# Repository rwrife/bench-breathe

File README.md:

# Bench Breathe

USB-powered ESP32-C3 workshop air-quality logger that tracks PM2.5 and VOC trends locally to help makers improve ventilation habits without cloud accounts.

## Overview

Bench Breathe is a low-voltage, local-first open-hardware project for hobby workshops and desk labs. It samples particulate and VOC indicators with temperature/humidity context, stores bounded trend history locally, and provides a local companion dashboard for setup, quality states, event notes, and explicit export.

**Bench Breathe is a non-certified advisory trend logger.** It does not determine whether air is safe and is not a medical, emergency, life-safety, or occupational-exposure instrument.

## Intended users and use cases

- Electronics hobbyists comparing trends during soldering or rework.
- 3D-printing users comparing baseline and active-print periods.
- Home workshop users recording manual actions such as opening a window or enabling an independently controlled extractor.
- Makers exporting their own local CSV/JSON data for troubleshooting and analysis.

## MVP workflow

1. Power the device from a reputable 5 V USB SELV source.
2. Connect from a phone/desktop browser on the local network or use USB serial fallback.
3. Complete time-bounded setup and baseline/warm-up prompts.
4. Record a work session and optional ventilation event labels.
5. Review local trends, freshness, quality states, and data gaps.
6. Export or delete local data through an explicit user action.

## Frozen MVP baseline

The normative baseline is in [`hardware/requirements.md`](hardware/requirements.md), with subsystem ownership, dependencies, evidence gates, and the risk register in [`PLAN.md`](PLAN.md).

Key constraints:

- USB 5 V SELV only; <=250 mA steady-state target and <=500 mA peak.
- PM2.5, VOC proxy/index, temperature, and humidity trend channels.
- Default 2 s acquisition, bounded local retention, and deterministic rollover.
- Local HTTP/JSON app interface with USB serial setup/recovery/export fallback.
- Offline sampling without mandatory internet, cloud account, or outbound telemetry.
- Editable KiCad hardware sources and schematic-owned Manufacturer/MPN BOM data.
- Advisory trend language only; static, simulation, bench, and field evidence remain distinct.

## Explicit non-goals and safety limits

- **No mains wiring or control.** No relays, fan switching, actuators, machinery control, or safety interlocks.
- **No hazardous-voltage or USB-PD operation.** The project is nominal 5 V USB SELV only.
- **No medical, emergency, fire/smoke/gas-alarm, life-safety, or occupational-limit function.**
- **No certified accuracy or safe/unsafe determination.** Placement, warm-up, drift, contamination, airflow, and faults can produce misleading data.
- **No mandatory cloud service or internet access.**
- Indoor, dry, non-condensing hobby-workshop use only; not for outdoor, explosive, or industrial-process environments.

Users must follow tool/material manufacturer guidance and appropriate ventilation and PPE practice independently of this device.

## Architecture at a glance

- **Hardware:** USB input/protection/regulation, ESP32-C3, PM/VOC/temp-humidity interfaces, status/input, debug/test access, PCB, and enclosure interface.
- **Firmware:** deterministic acquisition, validity states, bounded retention, atomic configuration, versioned local API, and serial recovery.
- **Companion web app:** setup, status/history, event notes, configuration, explicit export/delete, and accessible advisory messaging.
- **Shared protocol:** [`docs/protocol.md`](docs/protocol.md) is finalized contract v1 (HTTP + USB-serial shapes, units, limits, errors, authorization). The firmware baseline still streams the v0-compatible serial line; adoption is tracked in `docs/release-checklist.md` (T-1).

The device remains authoritative for sensor state, timestamps, configuration limits, and retained records. The app presents that contract and must not turn null/invalid values into apparently valid measurements. For the MVP, compiled app assets are served by the device for offline same-origin use. A physical, time-bounded setup action issues the per-device local credential; this reduces casual LAN access but does not make cleartext HTTP confidential or safe for internet exposure.

## Source tree

- `hardware/requirements.md` — normative MVP requirements and safety boundaries
- `hardware/kicad/bench-breathe.kicad_pro` — editable KiCad project container
- `hardware/kicad/bench-breathe.kicad_sch` — editable A0 electrical schematic and schematic-owned BOM-property source
- `hardware/kicad/bench-breathe.kicad_pcb` — planned editable PCB
- `hardware/component-selection.md` — exact M2 parts, manufacturer-datasheet checks, static power budget, and dated availability snapshot
- `firmware/` — device firmware and verification
- `app/` — local companion web app
- `docs/protocol.md` — device/app contract (v1)
- `docs/bring-up.md` — integration bring-up procedure, wiring/pinouts, calibration, troubleshooting matrix, and evidence ledger
- `docs/release-checklist.md` — fabrication/release artifact gates and open tracked items
- `bom/bom.csv` — generated stuffed-BOM export from schematic properties (regenerate with `python3 bom/export_bom.py`, gate with `python3 bom/verify_bom.py`)
- `bom/README.md` — BOM workflow, sourcing/pricing policy, and file roles
- `bom/non-schematic-items.csv` — enclosure, cables, fasteners, adapter, power supply, and PCB fab with explicit planning status

The current `bom/preliminary-bom.csv` is the issue-#2 planning list reconciled against the schematic (`Schematic_Refs`/`Reconciliation` columns). It is not a fabrication-ready BOM; `bom/bom.csv` is the export artifact.

## Project status

| Milestone | Status |
|---|---|
| M1 — Requirements, architecture, safety, and risk baseline | Baseline documented |
| M2 — Datasheet-backed component selection | Static selection complete; physical validation not started |
| M3 — Editable KiCad schematic and ERC | Complete: clean KiCad 9 ERC plus static validation and PDF review export |
| M4 — Schematic-source BOM export | Complete: `bom/bom.csv` generated from schematic properties with reproducibility + no-fabricated-price gate (`bom/verify_bom.py`) |
| M5 — PCB layout and DRC | A0 evidence board complete: 0 DRC violations with 15 documented unrouted stubs — **not fab release** (see `hardware/pcb-notes.md` §Residuals and `docs/release-checklist.md`) |
| M6 — Firmware baseline | Baseline implemented + natively verified (19 unit tests, pinned device build). Bench flash/flash-recovery and power gating on hardware not performed |
| M7 — Companion app baseline | App MVP + contract v1 complete; 13/13 contract tests against the dev simulator only — never run against a real device |
| M8 — Integration and bench bring-up | Bring-up procedure, wiring/pinouts, and troubleshooting published (`docs/bring-up.md`); all bench steps unexecuted — no prototype exists |
| M9 — Mature fabrication/release bundle | Gate checklist published (`docs/release-checklist.md`); fab artifacts blocked on A1 stub closure |

The editable A0 schematic and its static ERC/analyzer evidence are complete,
as is the A0 evidence PCB (0 DRC violations, 15 documented unrouted stubs —
not fab release), the natively verified firmware baseline, and the
contract-tested companion app (simulator-evidence only). PCB fab export,
simulation, firmware/app builds on hardware, assembly, bench measurement,
field results, and certification are not claimed. See
`docs/bring-up.md` (bench procedure and evidence ledger) and
`docs/release-checklist.md` (release gates and open tracked items).

## Development start

```bash
git clone https://github.com/rwrife/bench-breathe.git
cd bench-breathe
```

Review `hardware/requirements.md`, `PLAN.md`, and the issue backlog before implementing a subsystem. Work should proceed in dependency order and attach the evidence named by the relevant milestone; documentation alone does not satisfy a hardware or physical-test gate.

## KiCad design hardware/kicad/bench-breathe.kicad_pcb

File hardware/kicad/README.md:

# KiCad hardware sources

`bench-breathe.kicad_sch` is the editable A0 electrical schematic. It stores exact Manufacturer/MPN/LCSC/Datasheet/Package/BOM Comments fields and implements USB power/data/CC sensing, the fixed 3.3 V regulator, controller, sensors, programming/debug, local status/button, and named test points.

Project-local functional symbols and the SGP40 land pattern live under `lib/`; `generate_schematic.py` regenerates the editable source, and `validate_schematic.py` checks critical datasheet pin maps, net assignments, BOM properties, ERC JSON, and the PDF export.

Reproduce the static evidence from the repository root:

```bash
python3 -m venv /tmp/bench-breathe-ksa-env
/tmp/bench-breathe-ksa-env/bin/pip install -r hardware/kicad/requirements.txt
KICAD_SYMBOL_DIR=/usr/share/kicad/symbols /tmp/bench-breathe-ksa-env/bin/python hardware/kicad/generate_schematic.py
kicad-cli sch erc hardware/kicad/bench-breathe.kicad_sch --format json --output hardware/kicad/reports/erc.json --exit-code-violations
kicad-cli sch export pdf hardware/kicad/bench-breathe.kicad_sch --output hardware/kicad/exports/bench-breathe-schematic.pdf
KICAD_SYMBOL_DIR=/usr/share/kicad/symbols /tmp/bench-breathe-ksa-env/bin/python hardware/kicad/validate_schematic.py --erc hardware/kicad/reports/erc.json --footprint-dir /usr/share/kicad/footprints
```

The zero-violation ERC and validator are **static schematic evidence only**. They do not prove PCB routing, signal integrity, radio performance, power transients, assembly, sensor accuracy, or physical operation.

Re-run the metadata gate from the repository root with:

```bash
python3 hardware/scripts/verify_component_selection.py
```

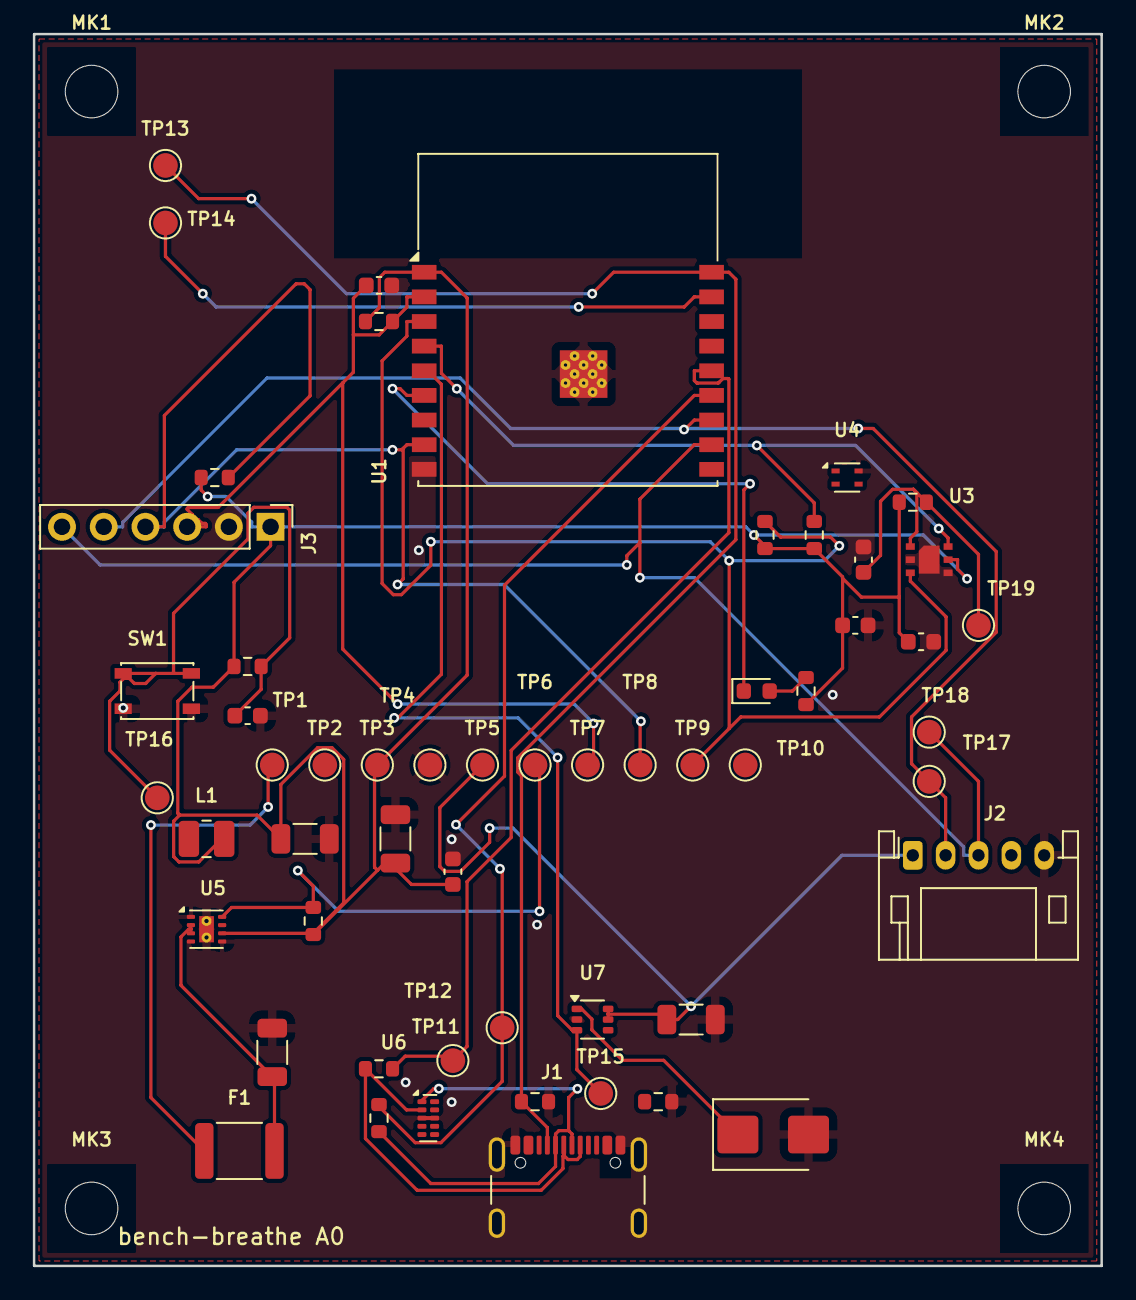
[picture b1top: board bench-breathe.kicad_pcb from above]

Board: 2 copper layers, 65.0 x 75.0 mm, 59 parts (0 on the bottom side), 24 nets.

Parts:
C1, C2, C3, C10: C_1206_3216Metric
C4, C5, C6, C7, C8, C9: C_0603_1608Metric
D1: D_SMB
D2: LED_0603_1608Metric
F1: Fuse_1812_4532Metric
J1: USB_C_Receptacle_GCT_USB4105-xx-A_16P_TopMnt_Hori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; USB_C_Receptacle_GCT_USB4105-xx-A_16P_TopMnt_Horizontal
J2: JST_PH_S5B-PH-K_1x05_P2.00mm_Horizontal
J3: PinHeader_1x06_P2.54mm_Vertical
L1: L_1008_2520Metric
MK1, MK2, MK3, MK4: MountingHole_3.2mm_M3
R1, R2, R3, R4, R5, R6, R7, R8, R9, R10, R11, R12: R_0603_1608Metric
SW1: SW_SPST_PTS810
TP1, TP2, TP3, TP4, TP5, TP6, TP7, TP8, TP9, TP10, TP11, TP12, TP13, TP14, TP15, TP16, TP17, TP18, TP19: TestPoint_Pad_D1.5mm
U1: ESP32-C3-WROOM-02
U3: Sensirion_DFN-6-1EP_2.44x2.44mm_P0.8mm
U4: Sensirion_DFN-4_1.5x1.5mm_P0.8mm_SHT4x_NoCentralP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; Sensirion_DFN-4_1.5x1.5mm_P0.8mm_SHT4x_NoCentralPad
U5: WSON-8-1EP_2x2mm_P0.5mm_EP0.9x1.6mm_ThermalVias
U6: USON-10_2.5x1.0mm_P0.5mm
U7: SOT-363_SC-70-6

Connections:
/+3V3: C2.1, C3.1, C4.1, C7.1, C8.1, J3.1, L1.2, R3.1, R4.1, R5.1, R6.1, R7.1, R8.1, R9.1, R10.1, TP3.1, U1.1, U3.5, U4.3, U5.6
/BOOT_GPIO9: J3.4, R10.2, TP8.1, U1.8
/CC1_SENSE: J1.A5, R1.1, TP13.1, U1.18, U6.4
/CC2_SENSE: J1.B5, R2.1, TP14.1, U1.17, U6.5
/EN: C5.1, J3.3, R4.2, TP7.1, U1.2
/GND: C1.2, C2.2, C3.2, C4.2, C5.2, C6.2, C7.2, C8.2, C9.2, C10.2, D1.2, J1.A1, J1.A12, J1.B1, J1.B12, J1.S1, J2.5, J3.2, R1.2, R2.2, SW1.2, TP4.1, U1.9, U1.19, U3.2, U3.4, U3.7, U4.4, U5.1, U5.4, U5.5, U5.9, U6.3, U6.8, U7.2
/I2C_SCL: R6.2, TP10.1, U1.4, U3.6, U4.2
/I2C_SDA: R5.2, TP9.1, U1.3, U3.3, U4.1
/PM_5V: C10.1, J2.1, TP5.1, U7.5, U7.6
/PM_ENABLE: TP15.1, U1.5, U7.3
/PM_UART_RX: J2.2, J3.5, TP17.1, U1.12
/PM_UART_TX: J2.3, J3.6, TP18.1, U1.11
/REG_PG: R3.2, TP6.1, U1.15, U5.8
/SGP_VDD: C6.1, R7.2, TP19.1, U3.1
/STATUS_LED_A: D2.2, R9.2
/STATUS_LED_K: D2.1, U1.6
/SW_NODE: L1.1, U5.7
/USB_CONN_DM: J1.A7, J1.B7, R11.1, U6.1
/USB_CONN_DP: J1.A6, J1.B6, R12.1, U6.2
/USB_DM: R11.2, TP12.1, U1.13
/USB_DP: R12.2, TP11.1, U1.14
/USER_BUTTON_N: C9.1, R8.2, SW1.1, TP16.1, U1.10
/VBUS: F1.1, J1.A4, J1.A9, J1.B4, J1.B9, TP1.1
/VBUS_FUSED: C1.1, D1.1, F1.2, TP2.1, U5.2, U5.3, U7.1

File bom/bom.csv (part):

Refs,Qty,Value,Description,Footprint,Package,Manufacturer,MPN,Supplier_Source,Estimated_Unit_Cost_USD,Price_Basis,DNP,Notes
"C1,C3,C10",3,10uF 10V X5R,,Capacitor_SMD:C_1206_3216Metric,C_1206_3216Metric,Murata,GRM31CR61A106KA01L,TBD - no validated source,TBD,TBD - live sourcing required at order time,,Buck input capacitor; close to VIN/PGND. | ESP32 local 3.3 V bulk capacitor. | Local switched PM rail bulk; controlled rise limits inrush.
C2,1,22uF 16V X5R,,Capacitor_SMD:C_1206_3216Metric,C_1206_3216Metric,Murata,GRM31CR61C226ME15L,TBD - no validated source,TBD,TBD - live sourcing required at order time,,Buck output capacitor; 22 µF nominal per TI recommended combination.
"C4,C6,C8,C9",4,100nF 50V X7R,,Capacitor_SMD:C_0603_1608Metric,C_0603_1608Metric,Murata,GRM188R71H104KA93D,TBD - no validated source,TBD,TBD - live sourcing required at order time,,ESP32 high-frequency supply bypass. | SGP40 filtered VDD decoupling after 10 Ω series resistor. | SHT40 local VDD bypass. | Button hardware debounce; firmware still applies bounded debounce.
"C5,C7",2,1uF 16V X7R,,Capacitor_SMD:C_0603_1608Metric,C_0603_1608Metric,Murata,GRM188R71C105KA12D,TBD - no validated source,TBD,TBD - live sourcing required at order time,,ESP32 EN power-on delay per module datasheet Figure 9-1. | SGP40 VDDH hotplate supply decoupling.
D1,1,SMBJ5.0A-13-F,Diodes Inc. unidirectional TVS clamp on fused VBUS,Diode_SMD:D_SMB,SMB / DO-214AA,Diodes Incorporated,SMBJ5.0A-13-F,LCSC C110528,0.1019,LCSC catalog snapshot 2026-09-05 (see hardware/component-selection.md),,"Unidirectional TVS: pin 1 cathode to VBUS_FUSED, pin 2 anode to GND."
D2,1,GREEN STATUS,"Green status LED (blink patterns, not color-only state)",LED_SMD:LED_0603_1608Metric,0603 green LED,Lite-On,LTST-C190KGKT,TBD - no validated source,TBD,TBD - live sourcing required at order time,,Active-low status LED. Firmware must use documented blink patterns so state is not conveyed by color alone.
F1,1,0.50A hold / 1.00A trip,"Resettable fuse, USB input protection",Fuse:Fuse_1812_4532Metric,1812 (4532 metric),Bourns,MF-MSMF050-2,LCSC C17313,0.0690,LCSC catalog snapshot 2026-09-05 (see hardware/component-selection.md),,Resettable input fault protection; not a precision USB current limiter.
J1,1,USB4105-GF-A,USB Type-C 5V sink receptacle with CC1/CC2 Rd sensing,Connector_USB:USB_C_Receptacle_GCT_USB4105-xx-A_16P_TopMnt_Horizontal,"USB Type-C receptacle, right-angle top-mount hybrid SMT/THT",GCT,USB4105-GF-A,LCSC C3020560,1.0624,LCSC catalog snapshot 2026-09-05 (see hardware/component-selection.md),,USB 2.0 5 V sink only. CC1/CC2 each use 5.1 kΩ Rd and feed ADC source-current sensing. No USB-PD.
J2,1,SPS30 HARNESS,Board-side JST PH harness header for off-board SPS30 PM module,Connector_JST:JST_PH_S5B-PH-K_1x05_P2.00mm_Horizontal,JST PH 1x5 2.00 mm side-entry,JST,S5B-PH-K-S(LF)(SN),TBD - no validated source,TBD,TBD - live sourcing required at order time,,"Board-side keyed harness header: 1=PM_5V, 2=RX, 3=TX, 4=SEL/floating, 5=GND. Verify assembled cable continuity."
J3,1,DEBUG / PROGRAM 3V3,"6-pin 3.3V debug/program header (EN, BOOT, U0TXD/RXD)",Connector_PinHeader_2.54mm:PinHeader_1x06_P2.54mm_Vertical,1x6 2.54 mm header,Samtec,TSW-106-07-G-S,TBD - no validated source,TBD,TBD - live sourcing required at order time,,"3.3 V only: pin 1=3V3, 2=GND, 3=EN, 4=BOOT/GPIO9, 5=U0TXD, 6=U0RXD."
L1,1,2.2uH 1.3A,Buck power inductor (TPS62162 recommended value),Inductor_SMD:L_1008_2520Metric,2.5 x 2.0 mm SMD,TDK,VLS252012T-2R2M1R3,TBD - no validated source,TBD,TBD - live sourcing required at order time,,"TPS6216x recommended inductor; 1.3 A current rating, verify saturation margin in layout/bench review."
"R1,R2",2,5.1k 1%,,Resistor_SMD:R_0603_1608Metric,0603 (1608 metric),Yageo,RC0603FR-075K1L,TBD - no validated source,TBD,TBD - live sourcing required at order time,,USB-C CC1 Rd; also forms CC1 ADC sense voltage. | USB-C CC2 Rd; also forms CC2 ADC sense voltage.
R3,1,100k 1%,,Resistor_SMD:R_0603_1608Metric,0603 (1608 metric),Yageo,RC0603FR-07100KL,TBD - no validated source,TBD,TBD - live sourcing required at order time,,TPS62162 open-drain PG pull-up.
"R4,R8,R10",3,10k 1%,,Resistor_SMD:R_0603_1608Metric,0603 (1608 metric),Yageo,RC0603FR-0710KL,TBD - no validated source,TBD,TBD - live sourcing required at order time,,ESP32 EN pull-up; EN must not float. | User-button pull-up to 3.3 V. | GPIO9 boot-strap pull-up; debug header may pull low for download mode.
"R5,R6",2,4.7k 1%,,Resistor_SMD:R_0603_1608Metric,0603 (1608 metric),Yageo,RC0603FR-074K7L,TBD - no validated source,TBD,TBD - live sourcing required at order time,,Single board-owned I2C SDA pull-up to 3.3 V. | Single board-owned I2C SCL pull-up to 3.3 V.
R7,1,10R 1%,,Resistor_SMD:R_0603_1608Metric,0603 (1608 metric),Yageo,RC0603FR-0710RL,TBD - no validated source,TBD,TBD - live sourcing required at order time,,SGP40 VDD RC decoupling series element per Figure 5.
R9,1,1k 1%,,Resistor_SMD:R_0603_1608Metric,0603 (1608 metric),Yageo,RC0603FR-071KL,TBD - no validated source,TBD,TBD - live sourcing required at order time,,Status LED current limit; approximately 1–2 mA at 3.3 V.
"R11,R12",2,0R 1%,,Resistor_SMD:R_0603_1608Metric,0603 (1608 metric),Yageo,RC0603FR-070RL,TBD - no validated source,TBD,TBD - live sourcing required at order time,,USB D- configuration link; 0 Ω follows Espressif Figure 9-1 and permits later SI tuning. | USB D+ configuration link; 0 Ω follows Espressif Figure 9-1 and permits later SI tuning.
SW1,1,SETUP / EVENT / RESET,"Tactile button for event marking, setup hold, reset hold",Button_Switch_SMD:SW_SPST_PTS810,SMD tactile switch,C&K,PTS810SJM250SMTRLFS,TBD - no validated source,TBD,TBD - live sourcing required at order time,,"Active-low local button. Firmware distinguishes event, setup hold, and factory-reset hold with explicit confirmation."
U1,1,ESP32-C3-WROOM-02-N4,Espressif ESP32-C3 Wi-Fi + native-USB MCU module,RF_Module:ESP32-C3-WROOM-02,"ESP32-C3-WROOM-02 module, 18.0 x 20.0 x 3.2 mm",Espressif Systems,ESP32-C3-WROOM-02-N4,LCSC C2934560,3.2912,LCSC catalog snapshot 2026-09-05 (see hardware/component-selection.md),,Native USB on pins 13/14; CC ADC sensing on GPIO0/1; antenna keepout required; GPIO2/8/9 strapping reviewed.
U2,1,SPS30,"Sensirion SPS30 particulate matter sensor (off-board, UART)",,Module with JST ZHR-5 mating connector,Sensirion AG,SPS30,TBD - no validated source,TBD,TBD - live sourcing required at order time,,Off-board PM module. UART selected by leaving SEL floating; housing is internally tied to signal GND.
U3,1,SGP40-D-R4,Sensirion SGP40 VOC index sensor (I2C 0x59),bench-breathe:Sensirion_DFN-6-1EP_2.44x2.44mm_P0.8mm,"DFN-6, 2.44 x 2.44 x 0.85 mm, center pad",Sensirion AG,SGP40-D-R4,LCSC C2874215,6.8654,LCSC catalog snapshot 2026-09-05 (see hardware/component-selection.md),,"I2C 0x59. VDD uses 10 Ω/100 nF RC, VDDH uses 1 µF; EP and pin 4 to GND; no board wash."
U4,1,SHT40-AD1B-R2,Sensirion SHT40 temperature/humidity sensor (I2C 0x44),Sensor_Humidity:Sensirion_DFN-4_1.5x1.5mm_P0.8mm_SHT4x_NoCentralPad,"DFN-4, 1.5 x 1.5 x 0.5 mm, open cavity, no center land",Sensirion AG,SHT40-AD1B-R2,LCSC C2909890,2.0288,LCSC catalog snapshot 2026-09-05 (see hardware/component-selection.md),,"I2C 0x44. Open-cavity sensor requires airflow, no copper under cavity, and separation from heat."
U5,1,TPS62162DSGR,TI fixed 3.3V 1A synchronous buck regulator,Package_SON:WSON-8-1EP_2x2mm_P0.5mm_EP0.9x1.6mm_ThermalVias,"WSON-8 exposed pad (DSG), 2.0 x 2.0 mm",Texas Instruments,TPS62162DSGR,LCSC C40256,0.9697,LCSC catalog snapshot 2026-09-05 (see hardware/component-selection.md),,Fixed 3.3 V buck: FB and EP to AGND; 2.2 µH/22 µF output; tight switch loop required.
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
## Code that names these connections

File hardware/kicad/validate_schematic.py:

#!/usr/bin/env python3
"""Validate issue #3 schematic acceptance criteria and ERC evidence."""
from __future__ import annotations

import argparse
import json
import os
import re
import sys
from collections import defaultdict
from pathlib import Path

ROOT = Path(__file__).resolve().parents[2]
SCH = ROOT / "hardware/kicad/bench-breathe.kicad_sch"
PRO = ROOT / "hardware/kicad/bench-breathe.kicad_pro"
LIB = ROOT / "hardware/kicad/lib/bench-breathe.kicad_sym"
FP = ROOT / "hardware/kicad/lib/bench-breathe.pretty/Sensirion_DFN-6-1EP_2.44x2.44mm_P0.8mm.kicad_mod"
NOTES = ROOT / "hardware/schematic-notes.md"
PDF = ROOT / "hardware/kicad/exports/bench-breathe-schematic.pdf"


def fail(message: str) -> None:
    print(f"ERROR: {message}", file=sys.stderr)
    raise SystemExit(1)


def prop(component, name: str) -> str:
    value = component.get_property(name)
    if isinstance(value, dict):
        value = value.get("value")
    return "" if value is None else str(value)


def rounded(x: float, y: float) -> tuple[float, float]:
    return round(float(x), 3), round(float(y), 3)


def main() -> int:
    parser = argparse.ArgumentParser()
    parser.add_argument("--erc", type=Path, required=True)
    parser.add_argument(
        "--footprint-dir", type=Path,
        default=Path(os.environ.get("KICAD_FOOTPRINT_DIR", "/usr/share/kicad/footprints")),
        help="KiCad .pretty library root used to resolve assigned footprints",
    )
    args = parser.parse_args()
    for path in (SCH, PRO, LIB, FP, NOTES, PDF, args.erc):
        if not path.is_file():
            fail(f"missing required file: {path}")

    os.environ.setdefault("KICAD_SYMBOL_DIR", "/usr/share/kicad/symbols")
    from kicad_sch_api import get_symbol_cache, load_schematic
    cache = get_symbol_cache()
    symbol_dir = Path(os.environ["KICAD_SYMBOL_DIR"])
    if symbol_dir.is_dir():
        cache.discover_libraries([str(symbol_dir)])
    if not cache.add_library_path(str(LIB)):
        fail("could not load project symbol library")
    schematic = load_schematic(SCH)
    components = {c.reference: c for c in schematic.components.all()}
    definitions = {ref: cache.get_symbol(c.lib_id) for ref, c in components.items()}
    if missing := sorted(ref for ref, definition in definitions.items() if definition is None):
        fail(f"symbol definitions did not resolve: {missing}")

    required_refs = {"J1", "J2", "J3", "F1", "D1", "D2", "U1", "U2", "U3", "U4", "U5", "U6", "U7", "L1", "SW1"}
    if missing := sorted(required_refs - set(components)):
        fail(f"missing required functional blocks: {missing}")
    purchased = [c for c in components.values() if c.in_bom and not c.reference.startswith("#")]
    footprint_count = 0
    for component in purchased:
        if component.reference != "U2" and not component.footprint:
            fail(f"{component.reference} has no footprint")
        if component.footprint:
            footprint_count += 1
            library, name = component.footprint.split(":", 1)
            if library == "bench-breathe":
                footprint_path = ROOT / "hardware/kicad/lib/bench-breathe.pretty" / f"{name}.kicad_mod"
            else:
                footprint_path = args.footprint_dir / f"{library}.pretty" / f"{name}.kicad_mod"
            if not footprint_path.is_file():
                fail(f"{component.reference} footprint not found: {component.footprint} ({footprint_path})")
            pad_tokens = re.findall(r'\(pad\s+(?:"([^"]+)"|([^\s()]+))', footprint_path.read_text(encoding="utf-8"))
            pad_numbers = {quoted or bare for quoted, bare in pad_tokens if quoted or bare}
            symbol_pin_numbers = {str(pin.number) for pin in definitions[component.reference].pins}
            if missing_pads := sorted(symbol_pin_numbers - pad_numbers):
                fail(
                    f"{component.reference} symbol pins have no footprint pads in {component.footprint}: "
                    f"{missing_pads}"
                )
        for field in ("Manufacturer", "MPN", "Datasheet", "BOM Comments"):
            if not prop(component, field).strip():
                fail(f"{component.reference} missing {field}")

    expected_pins = {
        "U1": {"1":"3V3", "2":"EN", "9":"GND", "13":"GPIO18_USB_D-", "14":"GPIO19_USB_D+", "17":"GPIO1", "18":"GPIO0", "19":"GND"},
        "U2": {"1":"VDD", "2":"RX_SDA", "3":"TX_SCL", "4":"SEL", "5":"GND"},
        "U3": {"1":"VDD", "2":"VSS", "3":"SDA", "4":"GND", "5":"VDDH", "6":"SCL", "7":"EP_GND"},
        "U4": {"1":"SDA", "2":"SCL", "3":"VDD", "4":"VSS"},
        "U5": {"1":"PGND", "2":"VIN", "3":"EN", "4":"AGND", "5":"FB", "6":"VOS", "7":"SW", "8":"PG", "9":"EP_GND"},
        "U6": {"1":"D1+", "2":"D1-", "3":"GND", "4":"D2+", "5":"D2-", "8":"GND"},
        "U7": {"1":"IN", "2":"GND", "3":"ON", "4":"NC", "5":"QOD", "6":"VOUT"},
    }
    for ref, pin_map in expected_pins.items():
        for number, name in pin_map.items():
            pin = definitions[ref].get_pin(number)
            if pin is None or pin.name != name:
                fail(f"{ref}.{number}: expected {name!r}, got {getattr(pin, 'name', None)!r}")

    text = SCH.read_text(encoding="utf-8")
    label_pattern = re.compile(r'\(label\s+"([^"]+)"\s*\n\s*\(at\s+([-0-9.]+)\s+([-0-9.]+)')
    labels_at: dict[tuple[float, float], set[str]] = defaultdict(set)
    for net, x, y in label_pattern.findall(text):
        labels_at[rounded(float(x), float(y))].add(net)
    for point, nets in labels_at.items():
        if len(nets) > 1:
            fail(f"conflicting labels at {point}: {sorted(nets)}")

    def pin_point(ref: str, number: str) -> tuple[float, float]:
        c = components[ref]
        pin = definitions[ref].get_pin(number)
        if pin is None:
            fail(f"{ref} missing pin {number}")
        return rounded(c.position.x + pin.position.x, c.position.y - pin.position.y)

    expectations = {
        ("J1","A4"):"VBUS", ("J1","A5"):"CC1_SENSE", ("J1","B5"):"CC2_SENSE", ("J1","S1"):"GND",
        ("J1","A6"):"USB_CONN_DP", ("J1","A7"):"USB_CONN_DM",
        ("U1","13"):"USB_DM", ("U1","14"):"USB_DP", ("U1","18"):"CC1_SENSE", ("U1","17"):"CC2_SENSE",
        ("U1","3"):"I2C_SDA", ("U1","4"):"I2C_SCL", ("U1","5"):"PM_ENABLE", ("U1","10"):"USER_BUTTON_N",
        ("U5","2"):"VBUS_FUSED", ("U5","6"):"+3V3", ("U5","7"):"SW_NODE", ("U5","8"):"REG_PG",
        ("U7","1"):"VBUS_FUSED", ("U7","3"):"PM_ENABLE", ("U7","6"):"PM_5V",
        ("U2","1"):"PM_5V", ("U2","2"):"PM_UART_RX", ("U2","3"):"PM_UART_TX",
        ("U3","1"):"SGP_VDD", ("U3","3"):"I2C_SDA", ("U3","5"):"+3V3", ("U3","6"):"I2C_SCL",
        ("U4","1"):"I2C_SDA", ("U4","2"):"I2C_SCL", ("J3","3"):"EN", ("J3","4"):"BOOT_GPIO9",
        ("J3","5"):"PM_UART_RX", ("J3","6"):"PM_UART_TX",
    }
    for (ref, pin), net in expectations.items():
        actual = labels_at.get(pin_point(ref, pin), set())
        if net not in actual:
            fail(f"{ref}.{pin}: expected {net}, got {sorted(actual)}")

    required_nets = {"VBUS", "VBUS_FUSED", "+3V3", "GND", "PM_5V", "SW_NODE", "REG_PG", "EN", "BOOT_GPIO9", "I2C_SDA", "I2C_SCL", "USB_CONN_DP", "USB_CONN_DM", "USB_DP", "USB_DM", "CC1_SENSE", "CC2_SENSE", "PM_ENABLE", "USER_BUTTON_N", "STATUS_LED_K", "PM_UART_RX", "PM_UART_TX", "SGP_VDD"}
    observed = {net for nets in labels_at.values() for net in nets}
    if missing := sorted(required_nets - observed):
        fail(f"missing required nets: {missing}")

    erc = json.loads(args.erc.read_text(encoding="utf-8"))
    violations = [v for sheet in erc.get("sheets", []) for v in sheet.get("violations", [])]
    if violations:
        fail(f"native ERC has {len(violations)} violation(s)")
    if PDF.stat().st_size < 1000:
        fail("schematic PDF is unexpectedly small")
    if "static" not in NOTES.read_text(encoding="utf-8").lower():
        fail("schematic notes omit evidence boundary")

    print(f"PASS: native ERC violations={len(violations)} kicad={erc.get('kicad_version')}")
    print(f"PASS: components={len(components)} purchased={len(purchased)} resolved_footprints={footprint_count} required_functional_blocks={len(required_refs)}")
    print(f"PASS: critical_pin_net_mappings={len(expectations)} named_nets={len(required_nets)}")
    print(f"PASS: schematic_pdf_bytes={PDF.stat().st_size}")
    print("PASS: evidence_class=static_schematic; pcb=not_run simulation=not_run bench=not_run field=not_run")
    return 0


if __name__ == "__main__":
    raise SystemExit(main())
